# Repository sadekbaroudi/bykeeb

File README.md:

# bykeeb (baby yoda keyboard)

## overview
bykeeb stands for "Baby Yoda Keyboard"

This is a 36 key wireless keyboard using a seeed xiao nrf52840 controller, supporting choc, gateron low profile, and MX switches.

### key features
* 36 keys
* seeed xiao nrf52840 controller
* hotswap or direct solder support for choc, gateron low profile, and MX switches
* battery cutout in pcb for a 32mm x 20mm x 6mm battery
* battery through holes for soldering a JST connector or direct wire
* on/off switch
* reset switch

### important notes
* This keyboard is wireless only. You cannot use a xiao rp2040.
* The switch spacing on this board is what I call min-y standard-x spacing. This is 19mm x 16mm. In the pictures above, I'm using [CMY keycaps](https://github.com/sadekbaroudi/fingerpunch/tree/master/keycaps/CMY).

## firmware

Firmware is done in [ZMK](https://zmk.dev/), and can be found in the [zmk-fingerpunch-keyboards](https://github.com/sadekbaroudi/zmk-fingerpunch-keyboards) github repository, specifically in the `boards/shields/bykeeb` directory.

## build guide

see the [build guide](buildguide/README.md) for more info

## case

see the [case readme](cases/README.md) for more info

## fabrication

Use the `gerber.zip` found in the [pcb directory](pcb/mx-choc-ks-27/production). If you are using [jlcpcb](jlcpcb.com), you can also use the `bom.csv` and `positions.csv` to do PCBA

## LICENSE

Free to use for personal use only. Any derivitive work must reference the author by name, link to [https://github.com/sadekbaroudi/bykeeb](https://github.com/sadekbaroudi/bykeeb), and propagate this license text. No commercial use of this work or any of its derivatives.

THE CONTENT OF THIS REPOSITORY IS PROVIDED "AS IS", WITHOUT WARRANTY OF ANY KIND, EXPRESS OR IMPLIED, INCLUDING BUT NOT LIMITED TO THE WARRANTIES OF MERCHANTABILITY, FITNESS FOR A PARTICULAR PURPOSE AND NONINFRINGEMENT. IN NO EVENT SHALL THE AUTHORS OR COPYRIGHT HOLDERS BE LIABLE FOR ANY CLAIM, DAMAGES OR OTHER LIABILITY, WHETHER IN AN ACTION OF CONTRACT, TORT OR OTHERWISE, ARISING FROM, OUT OF OR IN CONNECTION WITH THE SOFTWARE/HARDWARE OR THE USE OR OTHER DEALINGS IN THE SOFTWARE/HARDWARE.

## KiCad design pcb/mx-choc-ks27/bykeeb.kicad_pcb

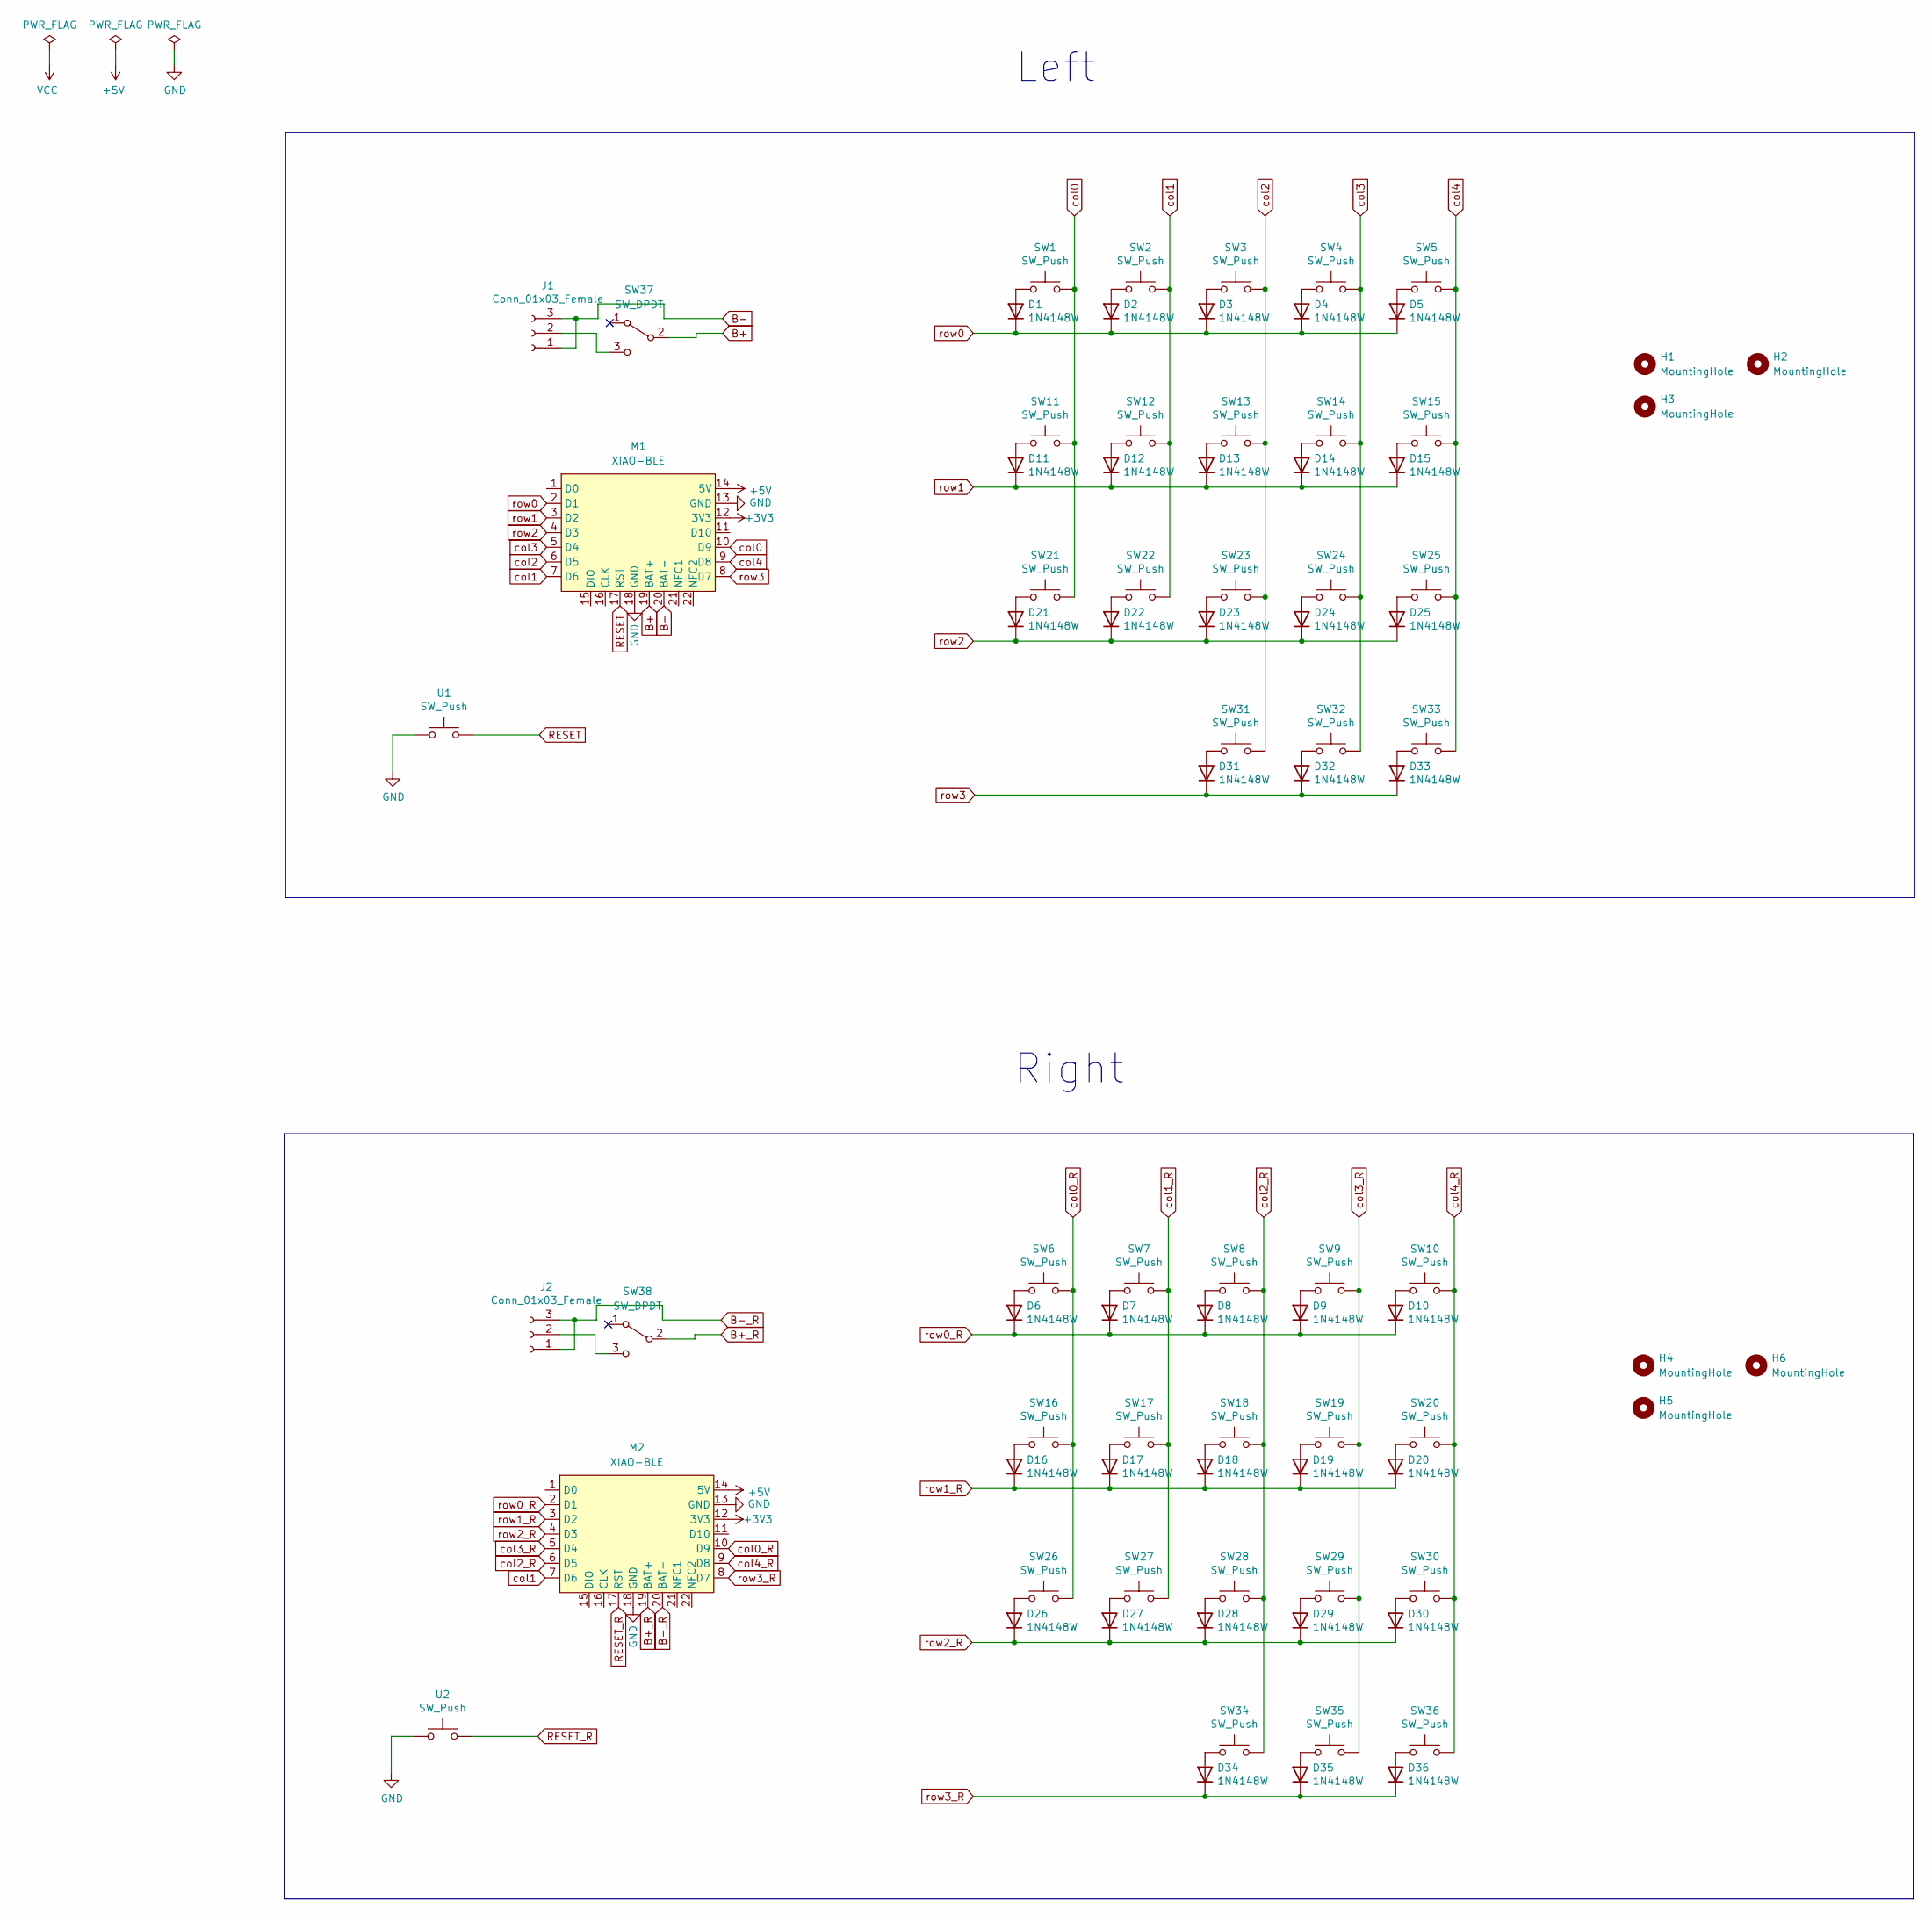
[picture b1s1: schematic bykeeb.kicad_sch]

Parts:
D1, D2, D3, D4, D5, D6, D7, D8, D9, D10, D11, D12, D13, D14, D15, D16, D17, D18, D19, D20, D21, D22, D23, D24, D25, D26, D27, D28, D29, D30, D31, D32, D33, D34, D35, D36: 1N4148W; D_SOD-123; LCSC C909967
H1, H2, H3, H4, H5, H6: MountingHole; MountingHole_2.2mm_M2_DIN965_Pad
J1, J2: Conn_01x03_Female; JST_PH_S3B-PH-K_1x03_P2.00mm_Horizontal; LCSC C157929
M1, M2: XIAO-BLE; xiao-ble-smd-cutout
SW1, SW2, SW3, SW4, SW5, SW6, SW7, SW8, SW9, SW10, SW11, SW12, SW13, SW14, SW15, SW16, SW17, SW18, SW19, SW20, SW21, SW22, SW23, SW24, SW25, SW26, SW27, SW28, SW29, SW30, SW31, SW32, SW33, SW34, SW35, SW36: SW_Push; gateron-ks27-choc-v1-mx-soldered-and-hotswap
SW37, SW38: SW_DPDT; MSK-12C02; LCSC C431540
U1, U2: SW_Push; SKQG-1155865

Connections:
+3V3: M1.12 (3V3), M2.12 (3V3)
+5V: M1.14 (5V), M2.14 (5V)
B+: M1.19 (BAT+), SW37.2 (B)
B+_R: M2.19 (BAT+), SW38.2 (B)
B-: J1.1, J1.3, M1.20 (BAT-)
B-_R: J2.1, J2.3, M2.20 (BAT-)
GND: M1.13 (GND), M1.18 (GND), M2.13 (GND), M2.18 (GND), U1.1, U2.1
unnamed: D1.2 (A), SW1.1
unnamed: D2.2 (A), SW2.1
unnamed: D3.2 (A), SW3.1
unnamed: D4.2 (A), SW4.1
unnamed: D5.2 (A), SW5.1
unnamed: D6.2 (A), SW6.1
unnamed: D7.2 (A), SW7.1
unnamed: D8.2 (A), SW8.1
unnamed: D9.2 (A), SW9.1
unnamed: D10.2 (A), SW10.1
unnamed: D11.2 (A), SW11.1
unnamed: D12.2 (A), SW12.1
unnamed: D13.2 (A), SW13.1
unnamed: D14.2 (A), SW14.1
unnamed: D15.2 (A), SW15.1
unnamed: D16.2 (A), SW16.1
unnamed: D17.2 (A), SW17.1
unnamed: D18.2 (A), SW18.1
unnamed: D19.2 (A), SW19.1
unnamed: D20.2 (A), SW20.1
unnamed: D21.2 (A), SW21.1
unnamed: D22.2 (A), SW22.1
unnamed: D23.2 (A), SW23.1
unnamed: D24.2 (A), SW24.1
unnamed: D25.2 (A), SW25.1
unnamed: D26.2 (A), SW26.1
unnamed: D27.2 (A), SW27.1
unnamed: D28.2 (A), SW28.1
unnamed: D29.2 (A), SW29.1
unnamed: D30.2 (A), SW30.1
unnamed: D31.2 (A), SW31.1
unnamed: D32.2 (A), SW32.1
unnamed: D33.2 (A), SW33.1
unnamed: D34.2 (A), SW34.1
unnamed: D35.2 (A), SW35.1
unnamed: D36.2 (A), SW36.1
unnamed: J1.2, SW37.3 (C)
unnamed: J2.2, SW38.3 (C)
RESET: M1.17 (RST), U1.2
RESET_R: M2.17 (RST), U2.2
col0: M1.10 (D9), SW1.2, SW11.2, SW21.2
col0_R: M2.10 (D9), SW6.2, SW16.2, SW26.2
col1: M1.7 (D6), M2.7 (D6), SW2.2, SW12.2, SW22.2
col1_R: SW7.2, SW17.2, SW27.2
col2: M1.6 (D5), SW3.2, SW13.2, SW23.2, SW31.2
col2_R: M2.6 (D5), SW8.2, SW18.2, SW28.2, SW34.2
col3: M1.5 (D4), SW4.2, SW14.2, SW24.2, SW32.2
col3_R: M2.5 (D4), SW9.2, SW19.2, SW29.2, SW35.2
col4: M1.9 (D8), SW5.2, SW15.2, SW25.2, SW33.2
col4_R: M2.9 (D8), SW10.2, SW20.2, SW30.2, SW36.2
row0: D1.1 (K), D2.1 (K), D3.1 (K), D4.1 (K), D5.1 (K), M1.2 (D1)
row0_R: D6.1 (K), D7.1 (K), D8.1 (K), D9.1 (K), D10.1 (K), M2.2 (D1)
row1: D11.1 (K), D12.1 (K), D13.1 (K), D14.1 (K), D15.1 (K), M1.3 (D2)
row1_R: D16.1 (K), D17.1 (K), D18.1 (K), D19.1 (K), D20.1 (K), M2.3 (D2)
row2: D21.1 (K), D22.1 (K), D23.1 (K), D24.1 (K), D25.1 (K), M1.4 (D3)
row2_R: D26.1 (K), D27.1 (K), D28.1 (K), D29.1 (K), D30.1 (K), M2.4 (D3)
row3: D31.1 (K), D32.1 (K), D33.1 (K), M1.8 (D7)
row3_R: D34.1 (K), D35.1 (K), D36.1 (K), M2.8 (D7)

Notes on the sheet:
Left
Right

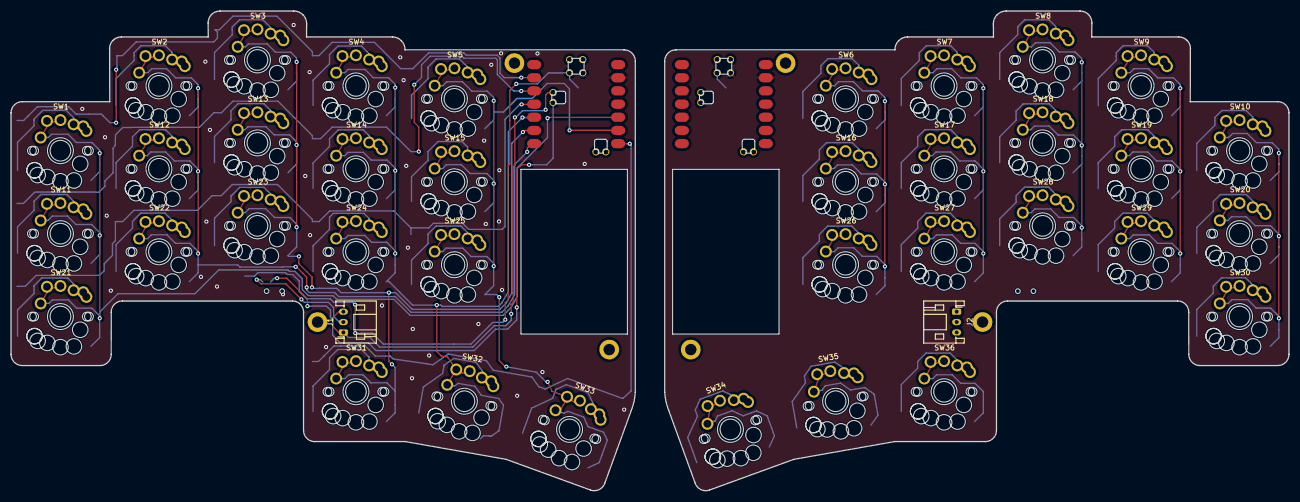
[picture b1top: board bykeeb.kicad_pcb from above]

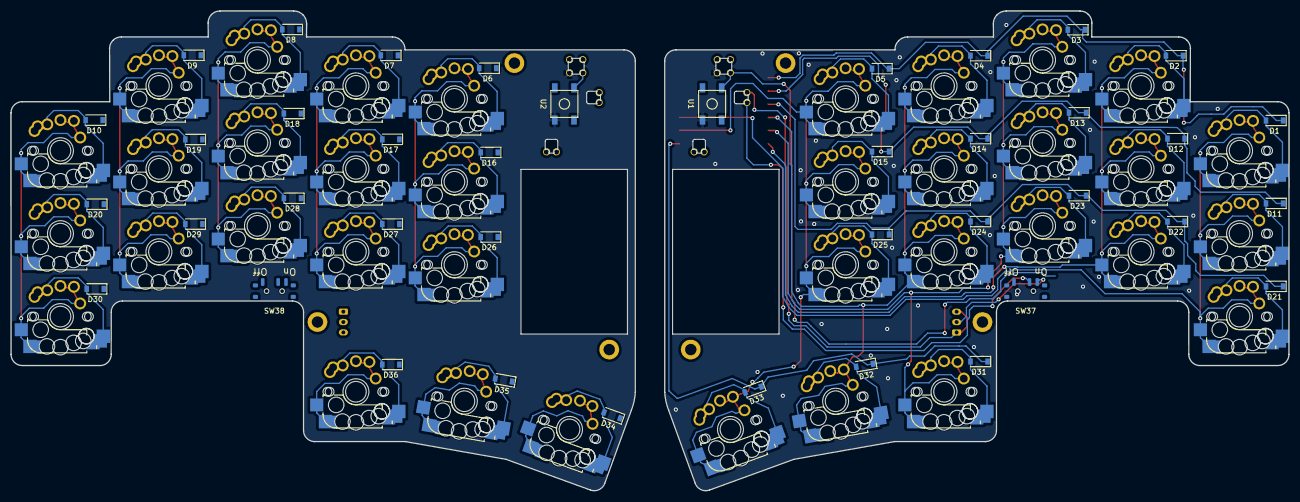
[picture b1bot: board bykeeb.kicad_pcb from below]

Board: 2 copper layers, 246.5 x 92.5 mm, 86 parts (40 on the bottom side), 65 nets.

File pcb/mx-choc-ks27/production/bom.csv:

Designator,Footprint,Quantity,Value,LCSC Part #
"D1, D10, D11, D12, D13, D14, D15, D16, D17, D18, D19, D2, D20, D21, D22, D23, D24, D25, D26, D27, D28, D29, D3, D30, D31, D32, D33, D34, D35, D36, D37, D38, D39, D4, D40, D44, D5, D51, D6, D7, D8, D9",D_SOD-123,42,1N4148W,C909967
J1,JST_PH_S3B-PH-K_1x03_P2.00mm_Horizontal,1,Conn_01x03_Female,C157929
J2,Connector_THT_1x4_2.54,1,Conn_01x04_Female,
"SW1, SW10, SW11, SW12, SW13, SW14, SW15, SW16, SW17, SW18, SW19, SW2, SW20, SW21, SW22, SW23, SW24, SW25, SW26, SW27, SW28, SW29, SW3, SW30, SW31, SW32, SW33, SW34, SW35, SW36, SW37, SW38, SW39, SW4, SW40, SW46, SW47, SW5, SW6, SW7, SW8, SW9",gateron-ks27-choc-v1-mx-soldered-and-hotswap,42,SW_Push,
SW41,SKQG-1155865,1,SW_Push,
SW42,MSK-12C02,1,SW_DPDT,C431540
U1,nice_nano,1,nice_nano,
U3,Elite-C,1,Elite-C,

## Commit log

2024-06-29 initial commit, almost done routing
2024-06-30 ready for prototype run
2024-06-30 mounting holes on each side in case we want to try out vik trackpoint support
2024-07-01 bykeeb case, reduced wall width, added lip to hold pcb at right height, bumpon recesses in bottom
2024-07-01 bykeeb svgs to help make a case
2024-07-01 case files with basic readme, and bykeeb step file
2024-07-02 fixed the cover, and added a carrying case with a print in place hinge
2024-07-03 added more bykeeb carrying case options
2024-07-03 reduced footprint version of bykeeb carrying case
2024-07-03 bykeeb carrying case with handles
2024-07-04 added versions with hinge clearance, in case the sides near the hinge are colliding
2024-07-04 added chamfer on cases inside, and reduced magnet hole depth to 2.6mm to let it stick out a tiny bit for better connection
2024-07-04 cleaned up unwanted carrying case files
2024-07-05 grogu emboss version and renamed existing cases to remove hinge-clearance, as all of them have it now
2024-07-05 svg for embossed carrying case
2024-07-10 added tighter case for better press fit pcb into body
2024-07-11 switch plates for bykeeb
2024-07-12 renamed stls that can be reversible, and added cover right side
2024-07-12 updated reset hole on right half of case body
2024-07-13 on off switch covers, short for carrying case, long otherwise
2024-07-13 choc and glp plates are actually the same
2024-07-14 better renders and updated parts and descripions
2024-07-15 final readmes
2024-07-15 added silkscreens to indicate battery polarity
2024-08-09 bykeeb body with inset 0.2mm for situations that requires for tighter pcb fit
2024-08-16 added two piece carrying case, and restructured cases folder a bit
2024-08-16 center piece for hinge-assembly-required carrying case
2024-08-18 updated existing hinge assembly required versions to include channel for better closing, and added new non-boxed versions
2024-09-23 fixed usb cutout location and added integrated cover plus switchplate combo stls
